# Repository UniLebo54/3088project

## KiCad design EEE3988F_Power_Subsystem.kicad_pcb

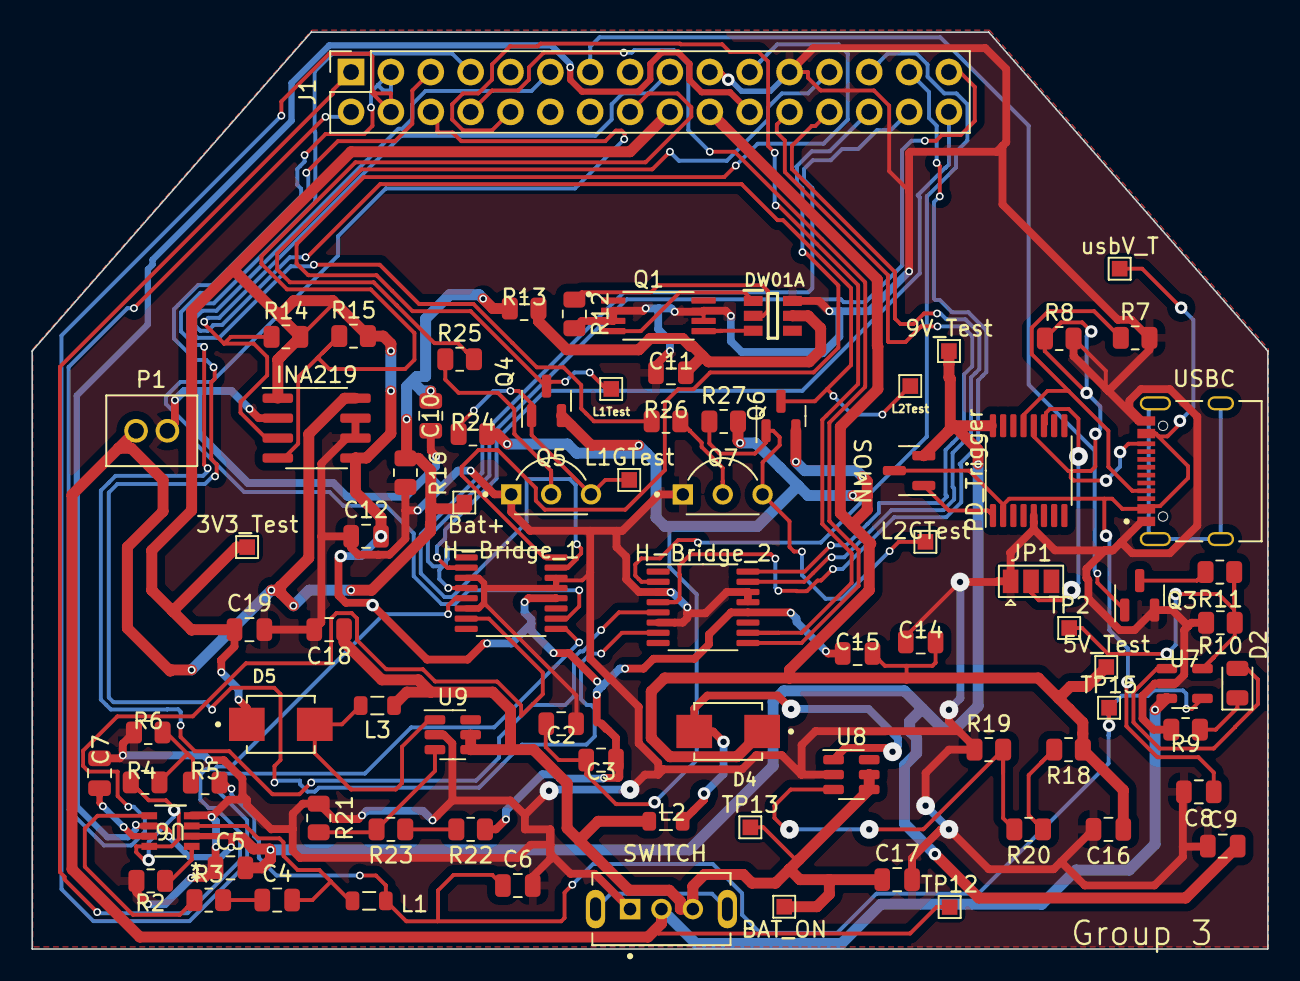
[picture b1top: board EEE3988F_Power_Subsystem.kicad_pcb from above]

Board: 2 copper layers, 78.7 x 58.4 mm, 83 parts (0 on the bottom side), 60 nets.

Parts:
3V3_Test: 3v3_Test; TestPoint_Pad_1.0x1.0mm
5V_Test: 5v_Test; TestPoint_Pad_1.0x1.0mm
9V_Test: PD_V; TestPoint_Pad_1.0x1.0mm
BAT_ON: BAT_ON; TestPoint_Pad_1.0x1.0mm
Bat+: batSupply; TestPoint_Pad_1.0x1.0mm
C2, C5, C9, C10, C14: 10uF; C_0805_2012Metric
C3, C15: 0.1uF; C_0805_2012Metric
C4, C11, C12: 100nF; C_0805_2012Metric
C6, C16, C17, C18, C19: 22uF; C_0805_2012Metric
C7, C8: 1uF; C_0805_2012Metric
D2: LED; LED_0805_2012Metric
D4, D5: SS24_R5G; DIOM4336X265N
DW01A: DW01A-G; SOT95P280X135-6N
H-Bridge_1, H-Bridge_2: DRV8833PW; TSSOP-16_4.4x5mm_P0.65mm
INA219: INA219AxD; SOIC-8_3.9x4.9mm_P1.27mm
J1: Conn_02x16_Odd_Even; PinSocket_2x16_P2.54mm_Vertical
JP1: SolderJumper_2_Open; SolderJumper-3_P1.3mm_Open_Pad1.0x1.5mm
L1: 10uH; L_0805_2012Metric
L1GTest: Load_1_G_Test; TestPoint_Pad_1.0x1.0mm
L1Test: load_1_Test; TestPoint_Pad_1.0x1.0mm
L2, L3: 22uH; L_0805_2012Metric
L2GTest: Load_2_G_Test; TestPoint_Pad_1.0x1.0mm
L2Test: load_2_Test; TestPoint_Pad_1.0x1.0mm
NMOS: AO3400A; SOT-23
P1: PHR-2; JST_PHR-2
PD_Trigger: IP2721; TSSOP-16_4.4x5mm_P0.65mm
Q1: FS8205A; SOP65P640X120-8N
Q3: BSS138; SOT-23
Q4, Q6: AO3401A; SOT-23
Q5, Q7: 2N2222A; TO92254P470H750-3
R2, R6, R14, R15, R19, R21, R24, R27: 10k; R_0805_2012Metric
R3: 20; R_0805_2012Metric
R4: 20k; R_0805_2012Metric
R5: 43k; R_0805_2012Metric
R7, R8: 5.1k; R_0805_2012Metric
R9, R12, R25, R26: 1k; R_0805_2012Metric
R10: 5k; R_0805_2012Metric
R11: 3.3k; R_0805_2012Metric
R13: 100; R_0805_2012Metric
R16: 0.0001k; R_0805_2012Metric
R18: 47k; R_0805_2012Metric
R20: 27k; R_0805_2012Metric
R22: 33k; R_0805_2012Metric
R23: 12k; R_0805_2012Metric
SWITCH: SS12D07VG4; SW_SS12D07VG4
TP2, TP12, TP13, TP15: TestPoint; TestPoint_Pad_1.0x1.0mm
U6: MP2315SGJ-Z; TSOT23-8_MP2315S_MNP
U7: MCP73831-2-OT; SOT-23-5
U8, U9: MT3608; SOT-23-6
USBC: TYPE-C-31-M-12; HRO_TYPE-C-31-M-12
usbV_T: usbc_V; TestPoint_Pad_1.0x1.0mm

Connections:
/3V3_Out: 3V3_Test.1, C12.2, C19.1, D5.C, H-Bridge_1.12 (VM), H-Bridge_2.12 (VM), INA219.1 (A1), INA219.5 (VS), J1.18, R14.2, R15.2, R22.1
/5V_Out: 5V_Test.1, C2.2, C3.2, C14.2, C15.2, C16.1, D4.C, J1.20, Q4.2 (S), Q6.2 (S), R18.1, R24.2, R27.2
/9V: 9V_Test.1, C5.2, C9.2, J1.22, NMOS.2 (S), PD_Trigger.16 (VBUS), U6.2 (IN), U6.6 (EN)
/BAT+: Bat+.1, C10.2, INA219.8 (IN+), P1.1, R13.2, R16.2, SWITCH.2, TP12.1, U7.3 (V_{BAT})
/CC1: PD_Trigger.13 (CC1), R7.1, USBC.A5 (CC1)
/CC2: PD_Trigger.12 (CC2), R8.1, USBC.B5 (CC2)
/CS: DW01A.2 (CS), R12.1
/CTRL_EXT_LOAD1: J1.25, R25.2
/CTRL_EXT_LOAD2: J1.7, R26.2
/EXT_LOAD1_OUT: J1.21, L1Test.1, Q4.3 (D)
/EXT_LOAD2_OUT: J1.11, L2Test.1, Q6.3 (D)
/G1: DW01A.1 (OD), Q1.4
/G2: DW01A.3 (OC), Q1.5
/I2C1_SCL: INA219.4 (SCL), J1.16, R15.1
/I2C1_SDA: INA219.3 (SDA), J1.17, R14.1
/MOTOR2_CTRL1: H-Bridge_1.9 (BIN1), J1.4
/MOTOR2_CTRL2: H-Bridge_1.10 (BIN2), J1.6
/MOTOR4_CTRL1: H-Bridge_2.9 (BIN1), J1.8
/MOTOR4_CTRL2: H-Bridge_2.10 (BIN2), J1.10
/MTR1_A_OUT: H-Bridge_1.2 (AOUT1), J1.32
/MTR1_B_OUT: H-Bridge_1.4 (AOUT2), J1.31
/MTR1_CTRL1: H-Bridge_1.16 (AIN1), J1.28
/MTR1_CTRL2: H-Bridge_1.15 (AIN2), J1.30
/MTR3_A_OUT: H-Bridge_2.2 (AOUT1), J1.27
/MTR3_B_OUT: H-Bridge_2.4 (AOUT2), J1.29
/MTR3_CTRL1: H-Bridge_2.16 (AIN1), J1.24
/MTR3_CTRL2: H-Bridge_2.15 (AIN2), J1.26
/Motor2_A_OUT: H-Bridge_1.7 (BOUT1), J1.2
/Motor2_B_OUT: H-Bridge_1.5 (BOUT2), J1.1
/Mtr4_A_OUT: H-Bridge_2.7 (BOUT1), J1.3
/Mtr4_B_OUT: H-Bridge_2.5 (BOUT2), J1.5
/PB4: J1.13, Q3.1 (G)
/SW: C6.1, L1.1, R5.2, TP15.1, U7.4 (V_{DD})
/VBUS: C8.1, NMOS.3 (D), PD_Trigger.2 (VIN), USBC.A4_B9 (VBUS), USBC.B4_A9 (VBUS), usbV_T.1
/VCC_DW: C11.2, DW01A.5 (VCC), R13.1
/V_BAT: BAT_ON.1, C17.1, C18.1, L2.1, L3.1, SWITCH.3, TP13.1, U8.4 (EN), U8.5 (IN), U9.4 (EN), U9.5 (IN)
GND: C2.1, C5.1, C6.2, C7.2, C8.2, C9.1, C10.1, C11.1, C12.1, C14.1, C16.2, C17.2, C18.2, C19.2, DW01A.6 (GND), H-Bridge_1.3 (AISEN), H-Bridge_1.6 (BISEN), H-Bridge_1.13 (GND), H-Bridge_1.14 (VINT), H-Bridge_2.3 (AISEN), H-Bridge_2.6 (BISEN), H-Bridge_2.13 (GND), H-Bridge_2.14 (VINT), INA219.2 (A0), INA219.6 (GND), INA219.7 (IN-), J1.19, J1.23, JP1.1 (A), P1.2, PD_Trigger.5 (GND), Q1.2, Q1.3, Q1.6, Q1.7, Q3.2 (S), Q5.1, Q7.1, R2.1, R6.1, R7.2, R8.2, R9.2, R10.1, R12.2, R16.1, R19.1, R21.1, SWITCH.1, U6.4 (GND), U7.2 (V_{SS}), U8.2 (GND), U9.2 (GND), USBC.A1_B12 (GND), USBC.B1_A12 (GND)
unnamed: C4.1, R3.2
unnamed: D2.2 (A), U7.1 (STAT)
unnamed: D2.1 (K), R9.1
unnamed: JP1.2 (B), PD_Trigger.11 (SEL)
unnamed: Q3.3 (D), R11.1
unnamed: L1GTest.1, Q4.1 (G), Q5.3, R24.1
unnamed: Q5.2, R25.1
unnamed: L2GTest.1, Q6.1 (G), Q7.3, R27.1
unnamed: Q7.2, R26.1
unnamed: NMOS.1 (G), PD_Trigger.1 (VBUSG)
unnamed: R4.2, R5.1, R6.2
unnamed: R18.2, R20.1
unnamed: R22.2, R23.1
unnamed: R2.2, U6.1 (AAM)
unnamed: R3.1, U6.5 (BST)
unnamed: R4.1, U6.8 (FB)
unnamed: C4.2, L1.2, U6.3 (SW)
unnamed: C7.1, U6.7 (VCC)
unnamed: R10.2, R11.2, TP2.1, U7.5 (PROG)
unnamed: R19.2, R20.2, U8.3 (FB)
unnamed: D4.A, L2.2, U8.1 (SW)
unnamed: R21.2, R23.2, U9.3 (FB)
unnamed: D5.A, L3.2, U9.1 (SW)

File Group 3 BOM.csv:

Reference,Value,Footprint,JLCPCB,Qty
"C1, C13",2.2uF,Capacitor_SMD:C_0805_2012Metric,,2
"C3, C5, C9, C10, C15",10uF,Capacitor_SMD:C_0805_2012Metric,,5
"C4, C11, C12",100nF,Capacitor_SMD:C_0805_2012Metric,,3
"C6, C16-19",22uF,Capacitor_SMD:C_0805_2012Metric,,5
"C7, C8",1uF,Capacitor_SMD:C_0805_2012Metric,,2
D2,LED,LED_SMD:LED_0805_2012Metric,,1
"D4, D5",SS24B,SS24_R5G:DIOM4336X265N,-- mixed values --,2
IC1,DW01A-G,DW01A-G:SOT95P280X135-6N,C2927799,1
J1,Conn_02x16_Odd_Even,Connector_PinSocket_2.54mm:PinSocket_2x16_P2.54mm_Vertical,,1
J4,TYPE-C-31-M-12,TYPE-C-31-M-12:HRO_TYPE-C-31-M-12,C165948,1
JP1,SolderJumper_2_Open,Jumper:SolderJumper-2_P1.3mm_Open_RoundedPad1.0x1.5mm,,1
L1,10uH,Inductor_SMD:L_0805_2012Metric,,1
"L2, L3",22uH,Inductor_SMD:L_0805_2012Metric,,2
P1,PHR-2,PHR-2:JST_PHR-2,C131339,1
Q1,FS8205A,FS8205A:SOP65P640X120-8N,C908265,1
Q3,BSS138,Package_TO_SOT_SMD:SOT-23,C8490,1
"Q4, Q6",AO3401A,Package_TO_SOT_SMD:SOT-23,C15127,2
"Q5, Q7",2N2222A,2N2222A:TO92254P470H750-3,C15127,2
Q8,AO3400A,Package_TO_SOT_SMD:SOT-23,C20917,1
"R2, R6, R14, R15, R19, R21, R24, R27",10k,Resistor_SMD:R_0805_2012Metric,,8
R3,20,Resistor_SMD:R_0805_2012Metric,,1
R4,20k,Resistor_SMD:R_0805_2012Metric,,1
R5,43k,Resistor_SMD:R_0805_2012Metric,,1
"R7, R8",5.1k,Resistor_SMD:R_0805_2012Metric,,2
"R9, R12, R25, R26",1k,Resistor_SMD:R_0805_2012Metric,,4
R10,5k,Resistor_SMD:R_0805_2012Metric,,1
R11,3.3k,Resistor_SMD:R_0805_2012Metric,,1
R13,100,Resistor_SMD:R_0805_2012Metric,,1
R16,0.1,Resistor_SMD:R_0805_2012Metric,,1
R18,47k,Resistor_SMD:R_0805_2012Metric,,1
R20,27k,Resistor_SMD:R_0805_2012Metric,,1
R22,33k,Resistor_SMD:R_0805_2012Metric,,1
R23,12k,Resistor_SMD:R_0805_2012Metric,,1
S1,SS12D07VG4,SS12D07VG4:SW_SS12D07VG4,C22435633,1
,,,,
TP2,MOT2,TestPoint:TestPoint_Pad_1.0x1.0mm,,1
TP3,PD_V,TestPoint:TestPoint_Pad_1.0x1.0mm,,1
TP4,usbc_V,TestPoint:TestPoint_Pad_1.0x1.0mm,,1
TP5,BAT_ON,TestPoint:TestPoint_Pad_1.0x1.0mm,,1
TP6,5v_Test,TestPoint:TestPoint_Pad_1.0x1.0mm,,1
TP7,3v3_Test,TestPoint:TestPoint_Pad_1.0x1.0mm,,1
TP8,load_1_Test,TestPoint:TestPoint_Pad_1.0x1.0mm,,1
TP9,Load_1_G_Test,TestPoint:TestPoint_Pad_1.0x1.0mm,,1
TP10,load_2_Test,TestPoint:TestPoint_Pad_1.0x1.0mm,,1
TP11,Load_2_G_Test,TestPoint:TestPoint_Pad_1.0x1.0mm,,1
TP12,MOT1,TestPoint:TestPoint_Pad_1.0x1.0mm,,1
U1,IP2721,Package_SO:TSSOP-16_4.4x5mm_P0.65mm,C603176,1
U3,INA219AxD,Package_SO:SOIC-8_3.9x4.9mm_P1.27mm,C1574856,1
"U4, U5",DRV8833PW,Package_SO:TSSOP-16_4.4x5mm_P0.65mm,C50506,2
U6,MP2315SGJ-Z,footprints:TSOT23-8_MP2315S_MNP,C3031493,1
U7,MCP73831-2-OT,Package_TO_SOT_SMD:SOT-23-5,C14879,1
"U8, U9",MT3608,Package_TO_SOT_SMD:SOT-23-6,C84817,2
